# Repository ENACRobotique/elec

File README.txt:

Repository for electronic circuits design

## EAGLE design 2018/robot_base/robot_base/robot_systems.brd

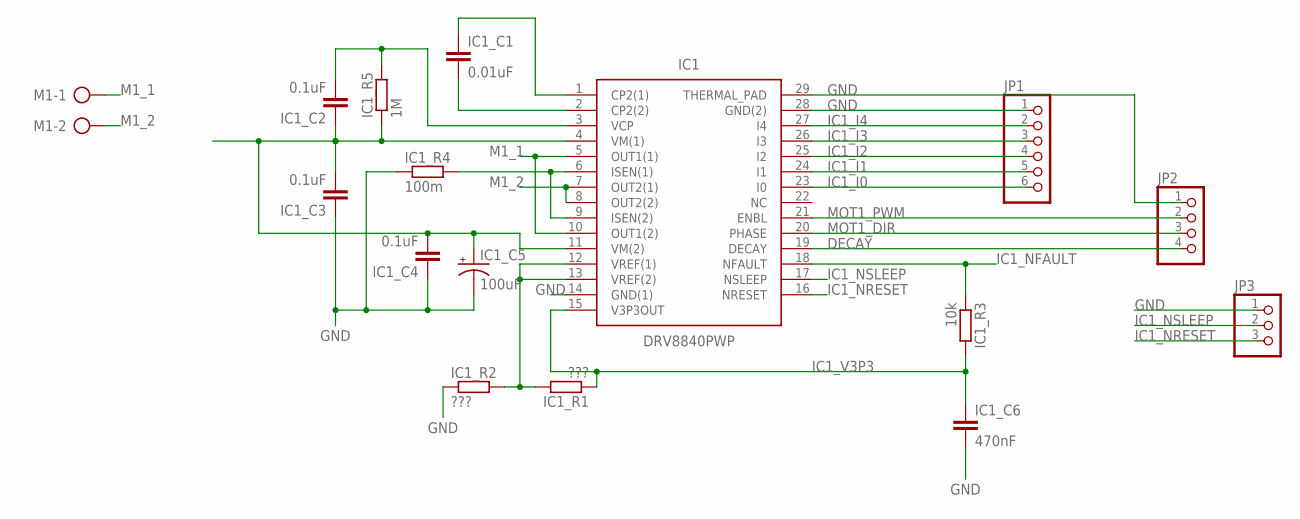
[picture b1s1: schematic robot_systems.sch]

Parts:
IC1: DRV8840PWP; SOP65P640X120-29N
IC1_C1: 0.01uF; C0603
IC1_C2, IC1_C3: 0.1uF; 0805
IC1_C4: 0.1uF; 1206
IC1_C5: 100uF; EIA7343
IC1_C6: 470nF; C0603
IC1_R1, IC1_R2: ???; 0204/5
IC1_R3: 10k; R2010
IC1_R4: 100m; R2512
IC1_R5: 1M; R0603
JP1: PINHD-1X6; 1X06
JP2: PINHD-1X4; 1X04
JP3: PINHD-1X3; 1X03
M1: AK500/2

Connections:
12V2: IC1.4 (VM(1)), IC1.11 (VM(2)), IC1_C2.1, IC1_C3.2, IC1_C4.2, IC1_C5.A (+), IC1_R5.1
DECAY: IC1.19 (DECAY), JP2.4
GND: IC1.14 (GND(1)), IC1.28 (GND(2)), IC1.29 (THERMAL_PAD), IC1_C3.1, IC1_C4.1, IC1_C5.C (-), IC1_C6.2, IC1_R2.1, IC1_R4.1, JP1.1, JP2.1, JP3.1
IC1_I0: IC1.23 (I0), JP1.6
IC1_I1: IC1.24 (I1), JP1.5
IC1_I2: IC1.25 (I2), JP1.4
IC1_I3: IC1.26 (I3), JP1.3
IC1_I4: IC1.27 (I4), JP1.2
IC1_NFAULT: IC1.18 (NFAULT), IC1_R3.1
IC1_NRESET: IC1.16 (NRESET), JP3.3
IC1_NSLEEP: IC1.17 (NSLEEP), JP3.2
IC1_V3P3: IC1.15 (V3P3OUT), IC1_C6.1, IC1_R1.1, IC1_R3.2
M1_1: IC1.5 (OUT1(1)), IC1.10 (OUT1(2)), M1.1
M1_2: IC1.7 (OUT2(1)), IC1.8 (OUT2(2)), M1.2
MOT1_DIR: IC1.20 (PHASE), JP2.3
MOT1_PWM: IC1.21 (ENBL), JP2.2
unnamed: IC1.12 (VREF(1)), IC1.13 (VREF(2)), IC1_R1.2, IC1_R2.2
unnamed: IC1.6 (ISEN(1)), IC1.9 (ISEN(2)), IC1_R4.2
unnamed: IC1.1 (CP2(1)), IC1_C1.1
unnamed: IC1.2 (CP2(2)), IC1_C1.2
unnamed: IC1.3 (VCP), IC1_C2.2, IC1_R5.2

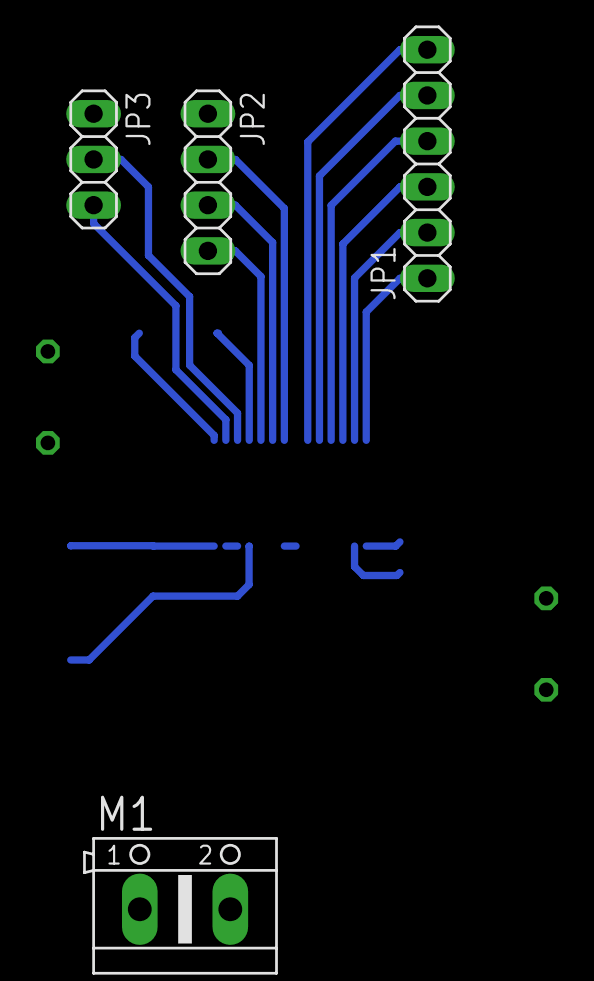
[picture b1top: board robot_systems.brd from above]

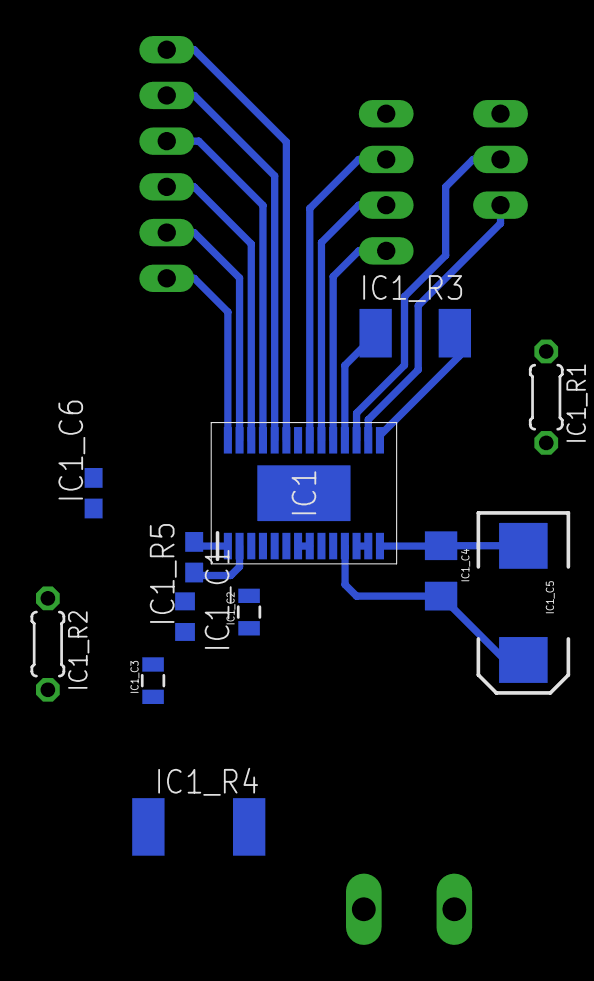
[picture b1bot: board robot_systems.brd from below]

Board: 2 copper layers, 16 parts (12 on the bottom side), 21 nets.

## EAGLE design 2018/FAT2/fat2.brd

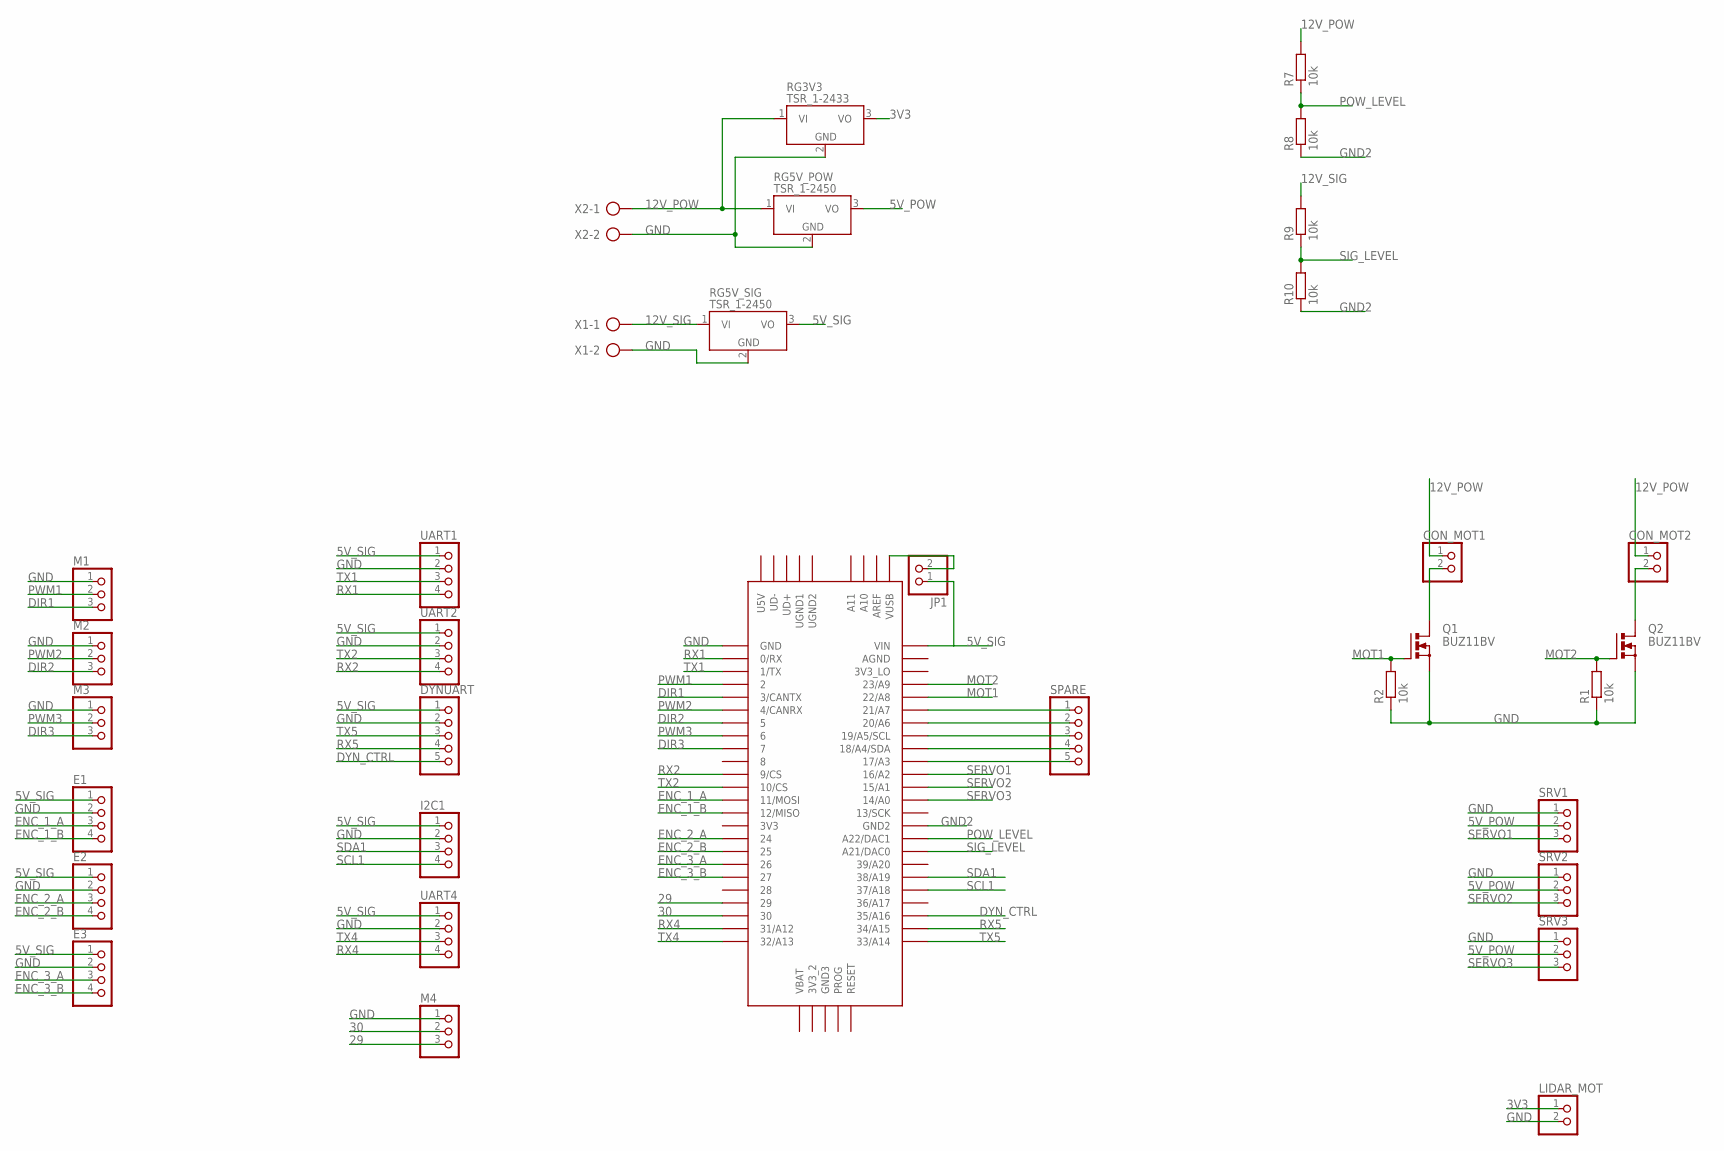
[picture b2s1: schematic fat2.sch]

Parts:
CON_MOT1, CON_MOT2: PINHD-1X2; 1X02
DYNUART: PINHD-1X5; 1X05
E1, E2, E3: PINHD-1X4; 1X04
I2C1: PINHD-1X4; 1X04
JP1: PINHD-1X2/90; 1X02/90
LIDAR_MOT: PINHD-1X2; 1X02
M1, M2, M3, M4: PINHD-1X3; 1X03
Q1, Q2: BUZ11BV; TO220BV
R1, R2, R7, R8, R9, R10: 10k; 0204/7
RG3V3: TSR_1-2433; TSR-1
RG5V_POW, RG5V_SIG: TSR_1-2450; TSR-1
SPARE: PINHD-1X5; 1X05
SRV1, SRV2, SRV3: PINHD-1X3; 1X03
U$1: TEENSY_3.5/3.6
UART1, UART2, UART4: PINHD-1X4; 1X04
X1, X2: AK300/2

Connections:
3V3: LIDAR_MOT.1, RG3V3.3 (VO)
5V_POW: RG5V_POW.3 (VO), SRV1.2, SRV2.2, SRV3.2
5V_SIG: DYNUART.1, E1.1, E2.1, E3.1, I2C1.1, JP1.1, RG5V_SIG.3 (VO), U$1.VIN, UART1.1, UART2.1, UART4.1
12V_POW: CON_MOT1.1, CON_MOT2.1, R7.2, RG3V3.1 (VI), RG5V_POW.1 (VI), X2.1
12V_SIG: R9.2, RG5V_SIG.1 (VI), X1.1
29: M4.3, U$1.29
30: M4.2, U$1.30
DIR1: M1.3, U$1.3/CANTX
DIR2: M2.3, U$1.5
DIR3: M3.3, U$1.7
DYN_CTRL: DYNUART.5, U$1.35/A16
ENC_1_A: E1.3, U$1.11/MOSI
ENC_1_B: E1.4, U$1.12/MISO
ENC_2_A: E2.3, U$1.24
ENC_2_B: E2.4, U$1.25
ENC_3_A: E3.3, U$1.26
ENC_3_B: E3.4, U$1.27
GND: DYNUART.2, E1.2, E2.2, E3.2, I2C1.2, LIDAR_MOT.2, M1.1, M2.1, M3.1, M4.1, Q1.S, Q2.S, R1.1, R2.1, RG3V3.2 (GND), RG5V_POW.2 (GND), RG5V_SIG.2 (GND), SRV1.1, SRV2.1, SRV3.1, U$1.GND, UART1.2, UART2.2, UART4.2, X1.2, X2.2
GND2: R8.1, R10.1, U$1.GND2
MOT1: Q1.G, R2.2, U$1.22/A8
MOT2: Q2.G, R1.2, U$1.23/A9
unnamed: SPARE.5, U$1.17/A3
unnamed: SPARE.4, U$1.18/A4/SDA
unnamed: CON_MOT1.2, Q1.D
unnamed: SPARE.3, U$1.19/A5/SCL
unnamed: CON_MOT2.2, Q2.D
unnamed: SPARE.2, U$1.20/A6
unnamed: JP1.2, U$1.VUSB
unnamed: SPARE.1, U$1.21/A7
POW_LEVEL: R7.1, R8.2, U$1.A22/DAC1
PWM1: M1.2, U$1.2
PWM2: M2.2, U$1.4/CANRX
PWM3: M3.2, U$1.6
RX1: U$1.0/RX, UART1.4
RX2: U$1.9/CS, UART2.4
RX4: U$1.31/A12, UART4.4
RX5: DYNUART.4, U$1.34/A15
SCL1: I2C1.4, U$1.37/A18
SDA1: I2C1.3, U$1.38/A19
SERVO1: SRV1.3, U$1.16/A2
SERVO2: SRV2.3, U$1.15/A1
SERVO3: SRV3.3, U$1.14/A0
SIG_LEVEL: R9.1, R10.2, U$1.21/DAC0 (A21/DAC0)
TX1: U$1.1/TX, UART1.3
TX2: U$1.10/CS, UART2.3
TX4: U$1.32/A13, UART4.3
TX5: DYNUART.3, U$1.33/A14

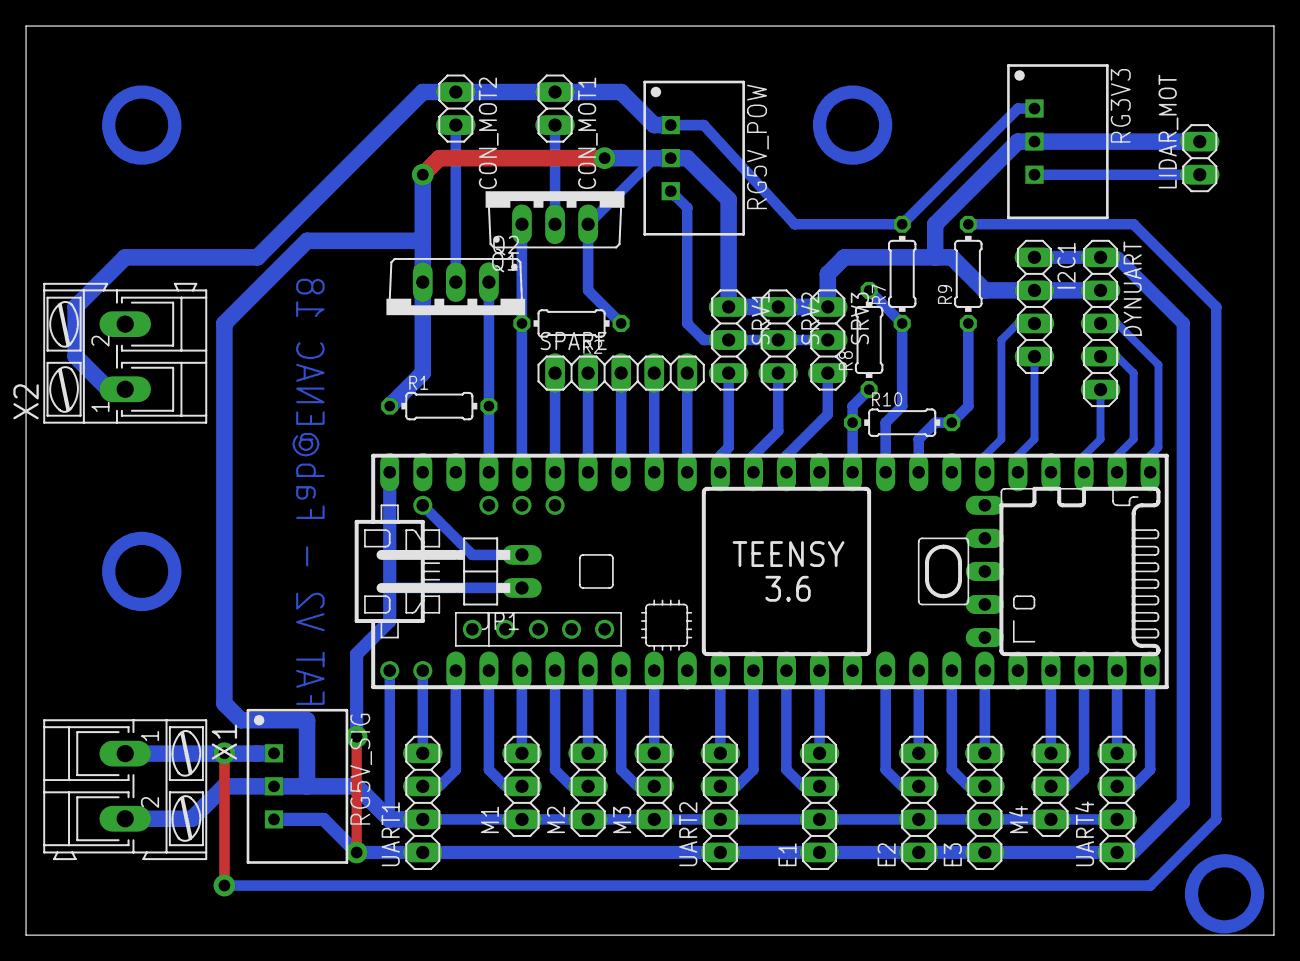
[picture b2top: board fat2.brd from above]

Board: 2 copper layers, 95.9 x 69.8 mm, 34 parts (0 on the bottom side), 47 nets.

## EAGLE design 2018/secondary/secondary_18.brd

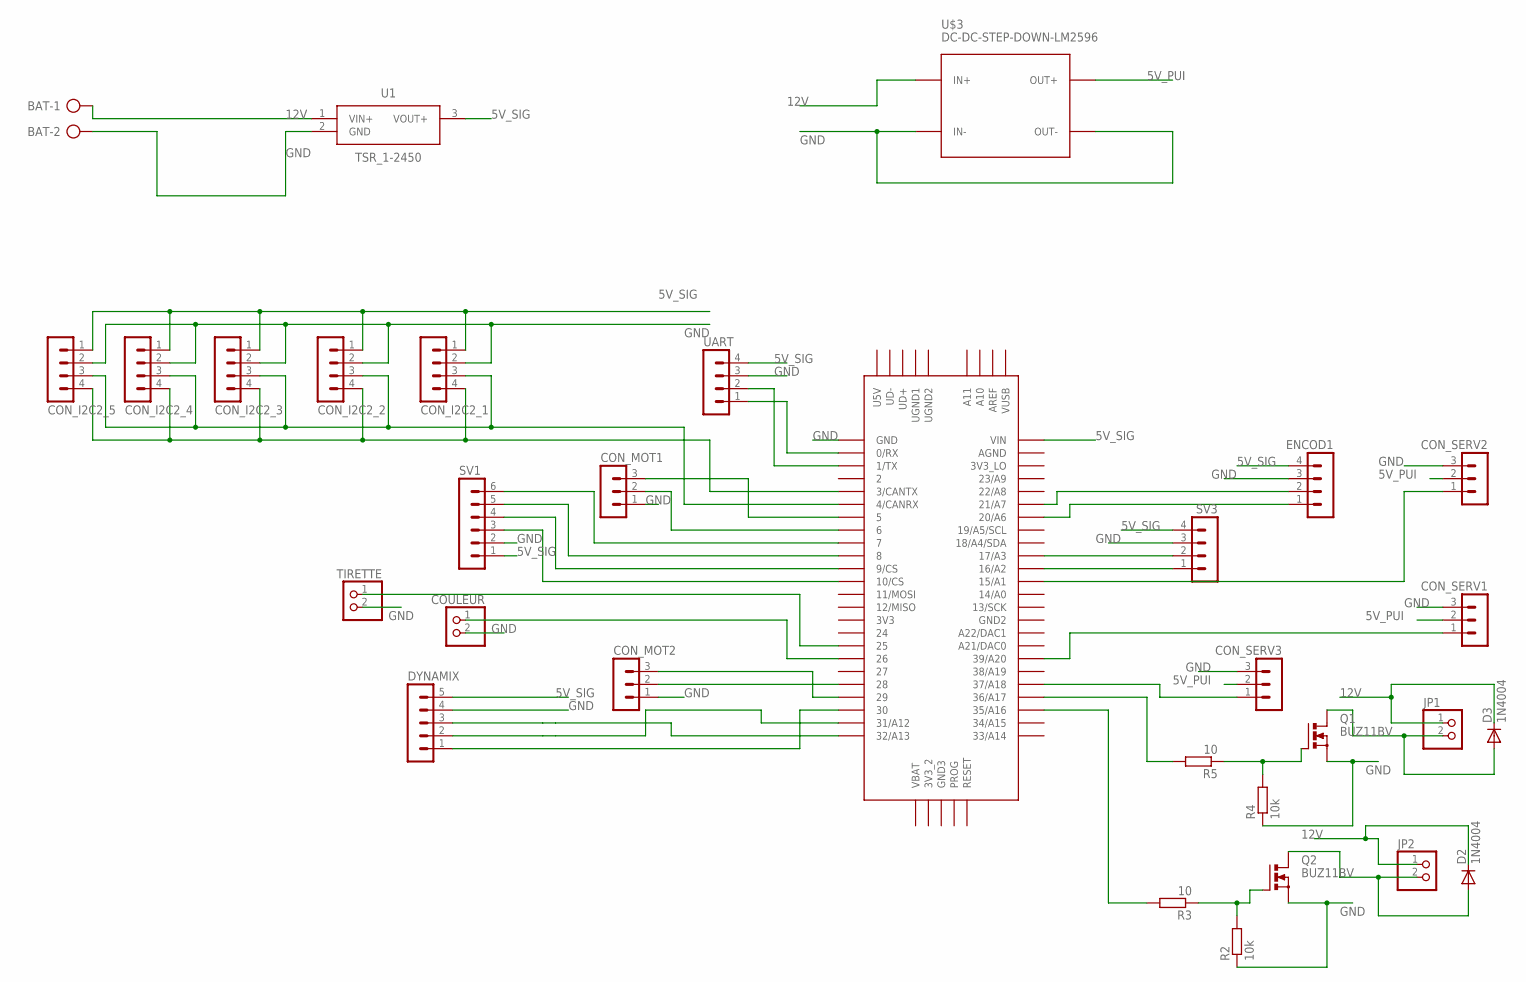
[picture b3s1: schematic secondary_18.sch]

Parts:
BAT: AK300/2
CON_I2C2_1, CON_I2C2_2, CON_I2C2_3, CON_I2C2_4, CON_I2C2_5: MA04-1
CON_MOT1, CON_MOT2: MA03-1
CON_SERV1, CON_SERV2, CON_SERV3: MA03-1
COULEUR: PINHD-1X2; 1X02
D2, D3: 1N4004; DO41-10
DYNAMIX: MA05-1
ENCOD1: MA04-1
JP1, JP2: PINHD-1X2; 1X02
Q1, Q2: BUZ11BV; TO220BV
R2, R4: 10k; 0204/7
R3, R5: 10; 0204/7
SV1: MA06-1
SV3: MA04-1
TIRETTE: PINHD-1X2; 1X02
U1: TSR_1-2450; TSR-1-24120
U$1: TEENSY_3.5/3.6
U$3: DC-DC-STEP-DOWN-LM2596
UART: MA04-1

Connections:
5V_PUI: CON_SERV1.2, CON_SERV2.2, CON_SERV3.2, U$3.OUT+
5V_SIG: CON_I2C2_1.1, CON_I2C2_2.1, CON_I2C2_3.1, CON_I2C2_4.1, CON_I2C2_5.1, DYNAMIX.5, ENCOD1.4, SV1.1, SV3.4, U1.3 (VOUT+), U$1.VIN, UART.4
12V: BAT.1, D2.C, D3.C, JP1.1, JP2.1, U1.1 (VIN+), U$3.IN+
GND: BAT.2, CON_I2C2_1.2, CON_I2C2_2.2, CON_I2C2_3.2, CON_I2C2_4.2, CON_I2C2_5.2, CON_MOT1.1, CON_MOT2.1, CON_SERV1.3, CON_SERV2.3, CON_SERV3.3, COULEUR.2, DYNAMIX.4, ENCOD1.3, Q1.S, Q2.S, R2.1, R4.1, SV1.2, SV3.3, TIRETTE.2, U1.2 (GND), U$1.GND, U$3.IN-, U$3.OUT-, UART.3
unnamed: CON_MOT2.3, U$1.29
unnamed: CON_MOT1.3, U$1.5
unnamed: CON_MOT1.2, U$1.6
unnamed: CON_MOT2.2, U$1.28
unnamed: Q2.G, R2.2, R3.1
unnamed: R3.2, U$1.35/A16
unnamed: D2.A, JP2.2, Q2.D
unnamed: SV3.1, U$1.16/A2
unnamed: Q1.G, R4.2, R5.1
unnamed: R5.2, U$1.36/A17
unnamed: D3.A, JP1.2, Q1.D
unnamed: SV3.2, U$1.17/A3
unnamed: ENCOD1.1, U$1.20/A6
unnamed: ENCOD1.2, U$1.21/A7
unnamed: CON_SERV2.1, U$1.15/A1
unnamed: CON_SERV3.1, U$1.37/A18
unnamed: DYNAMIX.3, U$1.32/A13
unnamed: CON_SERV1.1, U$1.39/A20
unnamed: DYNAMIX.2, U$1.31/A12
unnamed: CON_I2C2_1.4, CON_I2C2_2.4, CON_I2C2_3.4, CON_I2C2_4.4, CON_I2C2_5.4, U$1.3/CANTX
unnamed: COULEUR.1, U$1.26
unnamed: CON_I2C2_1.3, CON_I2C2_2.3, CON_I2C2_3.3, CON_I2C2_4.3, CON_I2C2_5.3, U$1.4/CANRX
unnamed: DYNAMIX.1, U$1.30
unnamed: TIRETTE.1, U$1.25
unnamed: U$1.1/TX, UART.2
unnamed: U$1.0/RX, UART.1
unnamed: SV1.3, U$1.10/CS
unnamed: SV1.4, U$1.9/CS
unnamed: SV1.5, U$1.8
unnamed: SV1.6, U$1.7

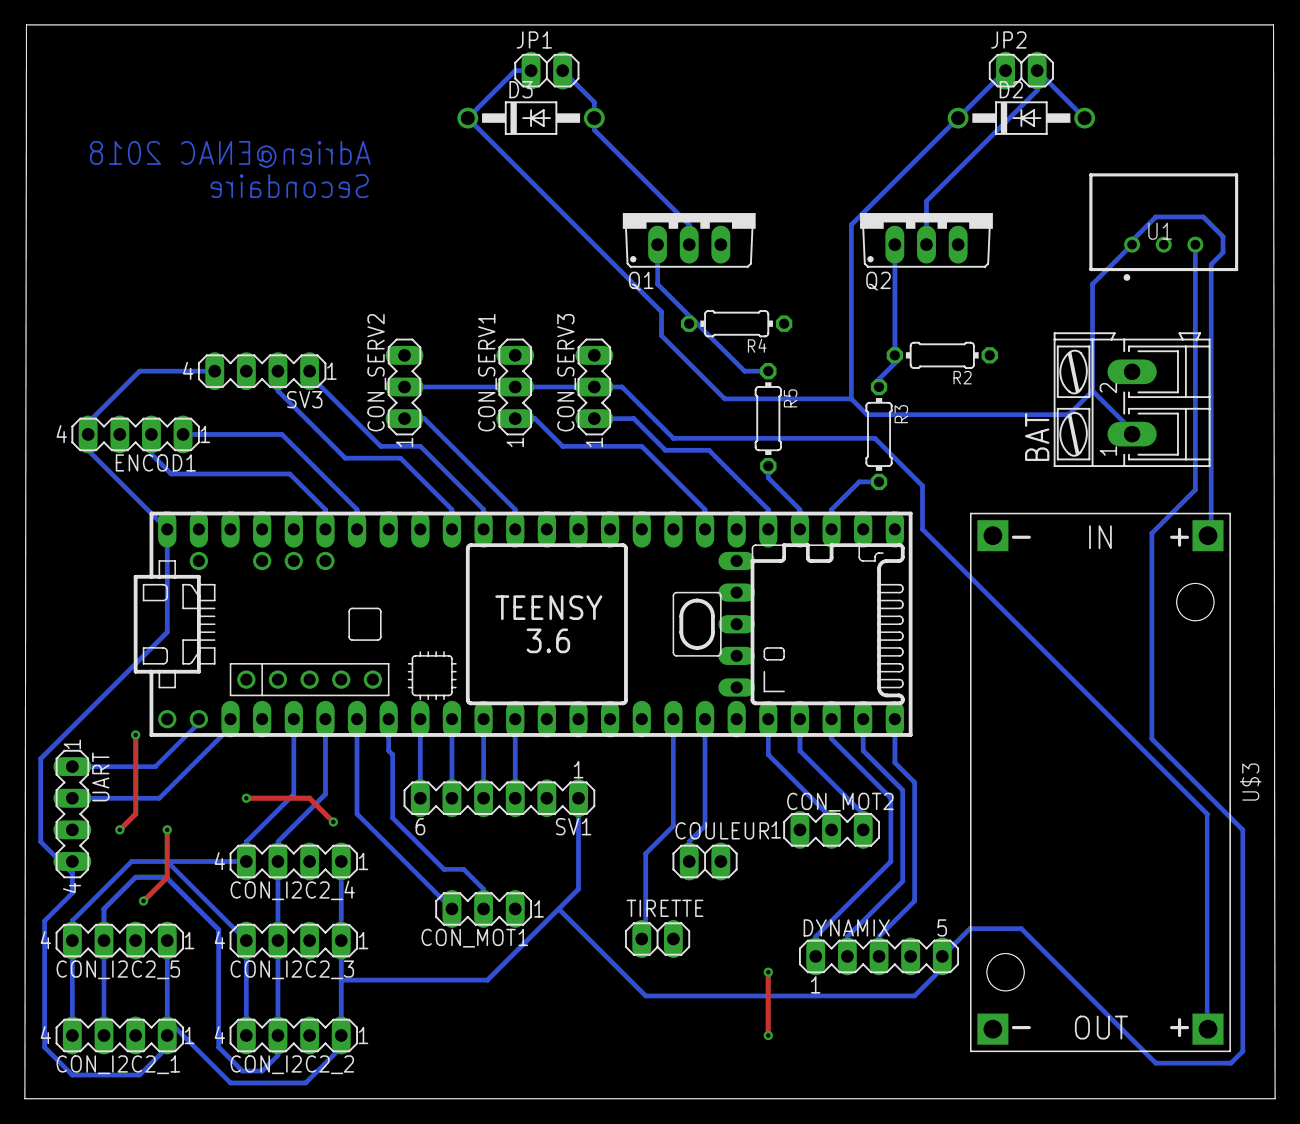
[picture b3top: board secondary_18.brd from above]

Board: 2 copper layers, 100.4 x 86.2 mm, 31 parts (0 on the bottom side), 34 nets.

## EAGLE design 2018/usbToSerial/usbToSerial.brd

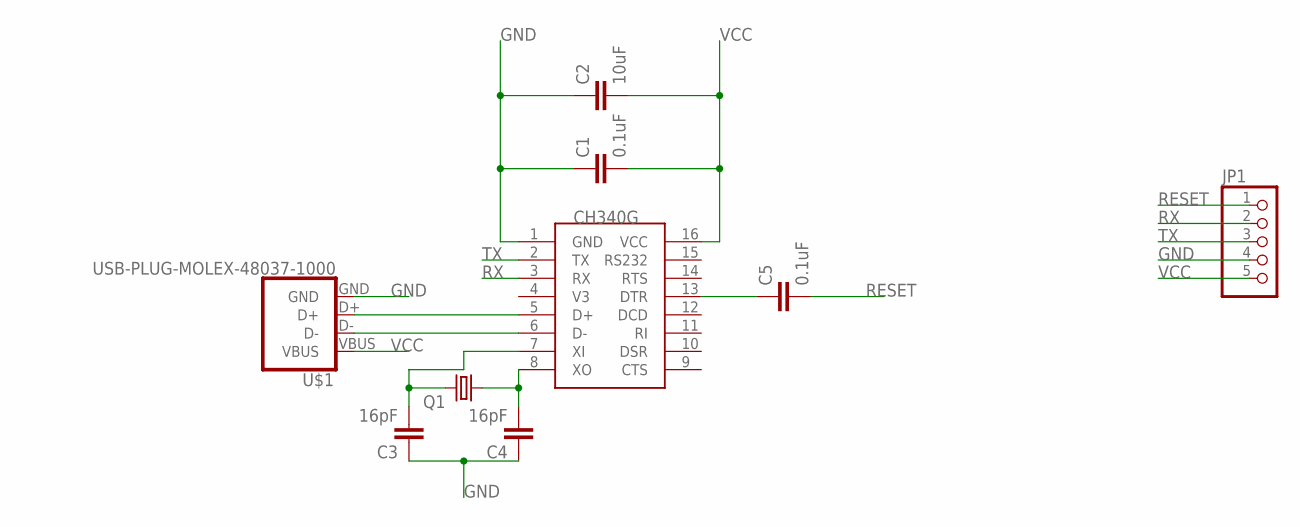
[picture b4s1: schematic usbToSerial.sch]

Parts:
C1, C5: 0.1uF; C0603
C2: 10uF; C3216
C3, C4: 16pF; C0603
JP1: PINHD-1X5/90; 1X05/90
Q1: CRYSTALSM49; SM49
U$1: USB-PLUG-MOLEX-48037-1000; MOLEX-48037-1000
U$2: CH340G; SOIC16

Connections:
GND: C1.1, C2.1, C3.1, C4.1, JP1.4, U$1.GND, U$2.1 (GND)
unnamed: U$1.D+, U$2.5 (D+)
unnamed: U$1.D-, U$2.6 (D-)
unnamed: C3.2, Q1.2, U$2.7 (XI)
unnamed: C4.2, Q1.1, U$2.8 (XO)
unnamed: C5.1, U$2.13 (DTR)
RESET: C5.2, JP1.1
RX: JP1.2, U$2.3 (RX)
TX: JP1.3, U$2.2 (TX)
VCC: C1.2, C2.2, JP1.5, U$1.VBUS, U$2.16 (VCC)

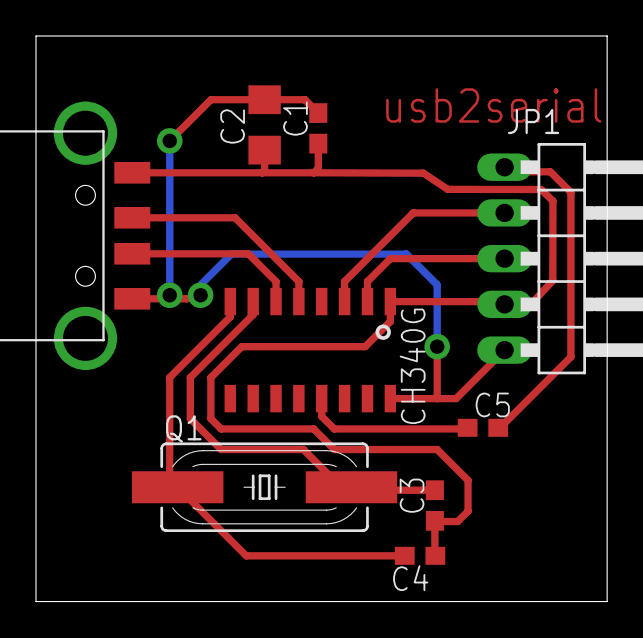
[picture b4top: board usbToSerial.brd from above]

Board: 2 copper layers, 31.7 x 31.4 mm, 9 parts (0 on the bottom side), 10 nets.

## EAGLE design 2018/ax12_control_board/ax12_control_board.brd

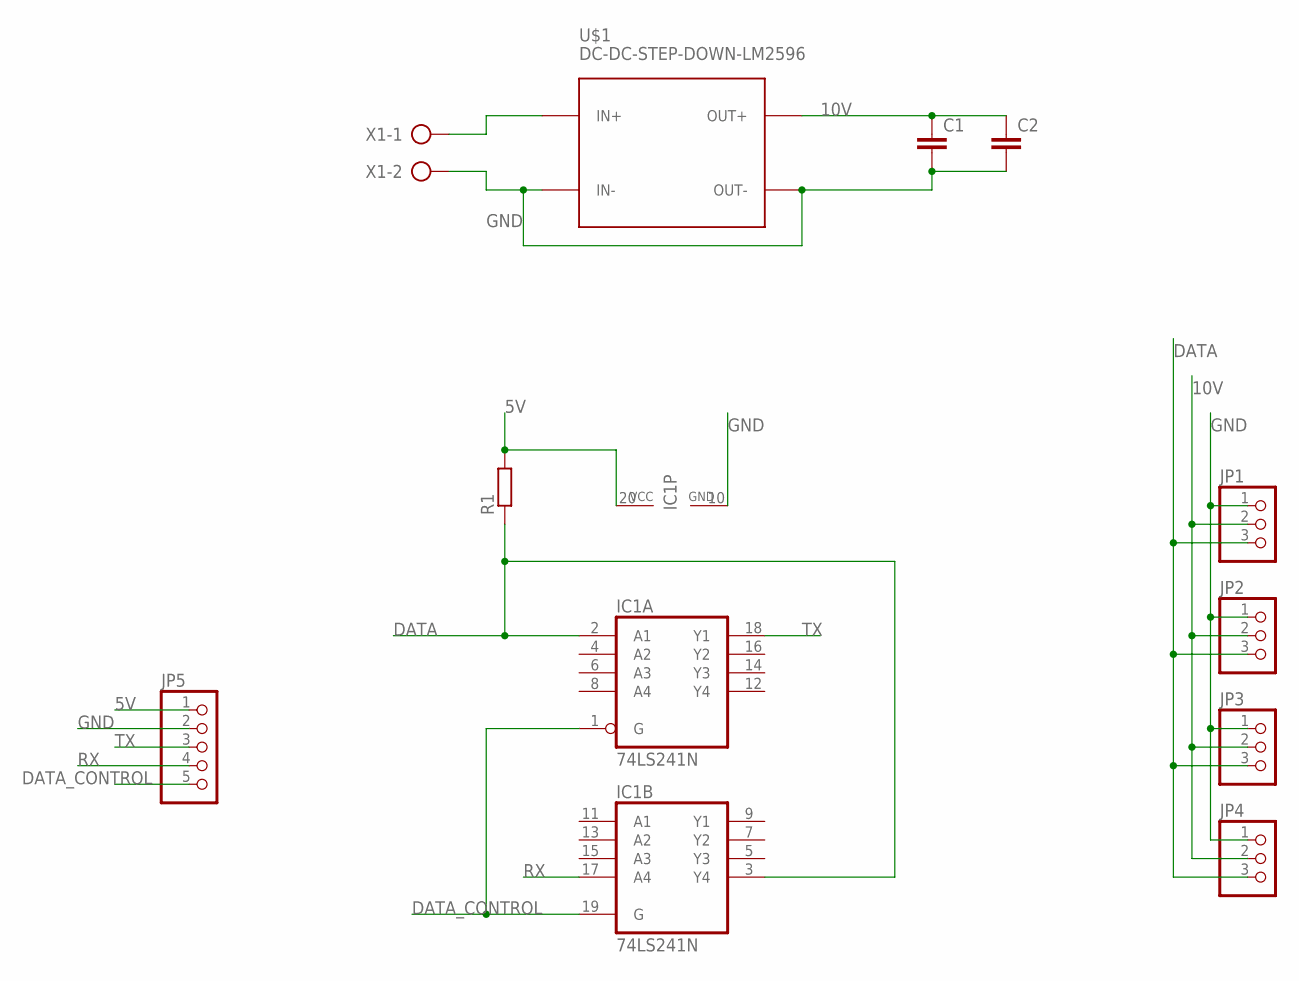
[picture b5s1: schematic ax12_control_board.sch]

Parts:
C1, C2: C-EU025-060X050; C025-060X050
IC1: 74LS241N; DIL20
JP1, JP2, JP3, JP4: PINHD-1X3; 1X03
JP5: PINHD-1X5; 1X05
R1: R-EU_0207/12; 0207/12
U$1: DC-DC-STEP-DOWN-LM2596
X1: AK300/2

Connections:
5V: IC1.20 (VCC), JP5.1, R1.2
10V: C1.1, C2.1, JP1.2, JP2.2, JP3.2, JP4.2, U$1.OUT+
DATA: IC1.2 (A1), IC1.3 (Y4), JP1.3, JP2.3, JP3.3, JP4.3, R1.1
DATA_CONTROL: IC1.1 (G), IC1.19 (G), JP5.5
GND: C1.2, C2.2, IC1.10 (GND), JP1.1, JP2.1, JP3.1, JP4.1, JP5.2, U$1.IN-, U$1.OUT-, X1.2
unnamed: U$1.IN+, X1.1
RX: IC1.17 (A4), JP5.4
TX: IC1.18 (Y1), JP5.3

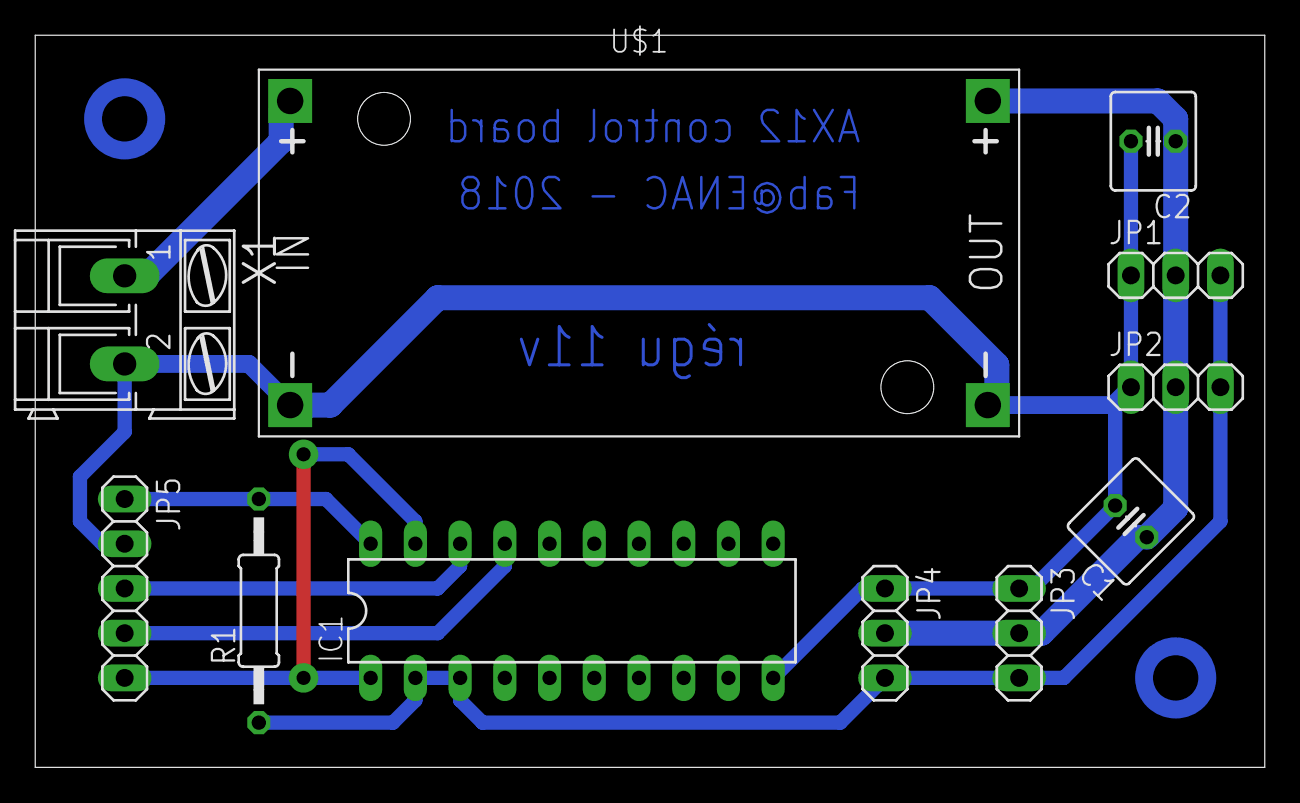
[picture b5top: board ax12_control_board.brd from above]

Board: 2 copper layers, 69.8 x 41.6 mm, 11 parts (0 on the bottom side), 8 nets.

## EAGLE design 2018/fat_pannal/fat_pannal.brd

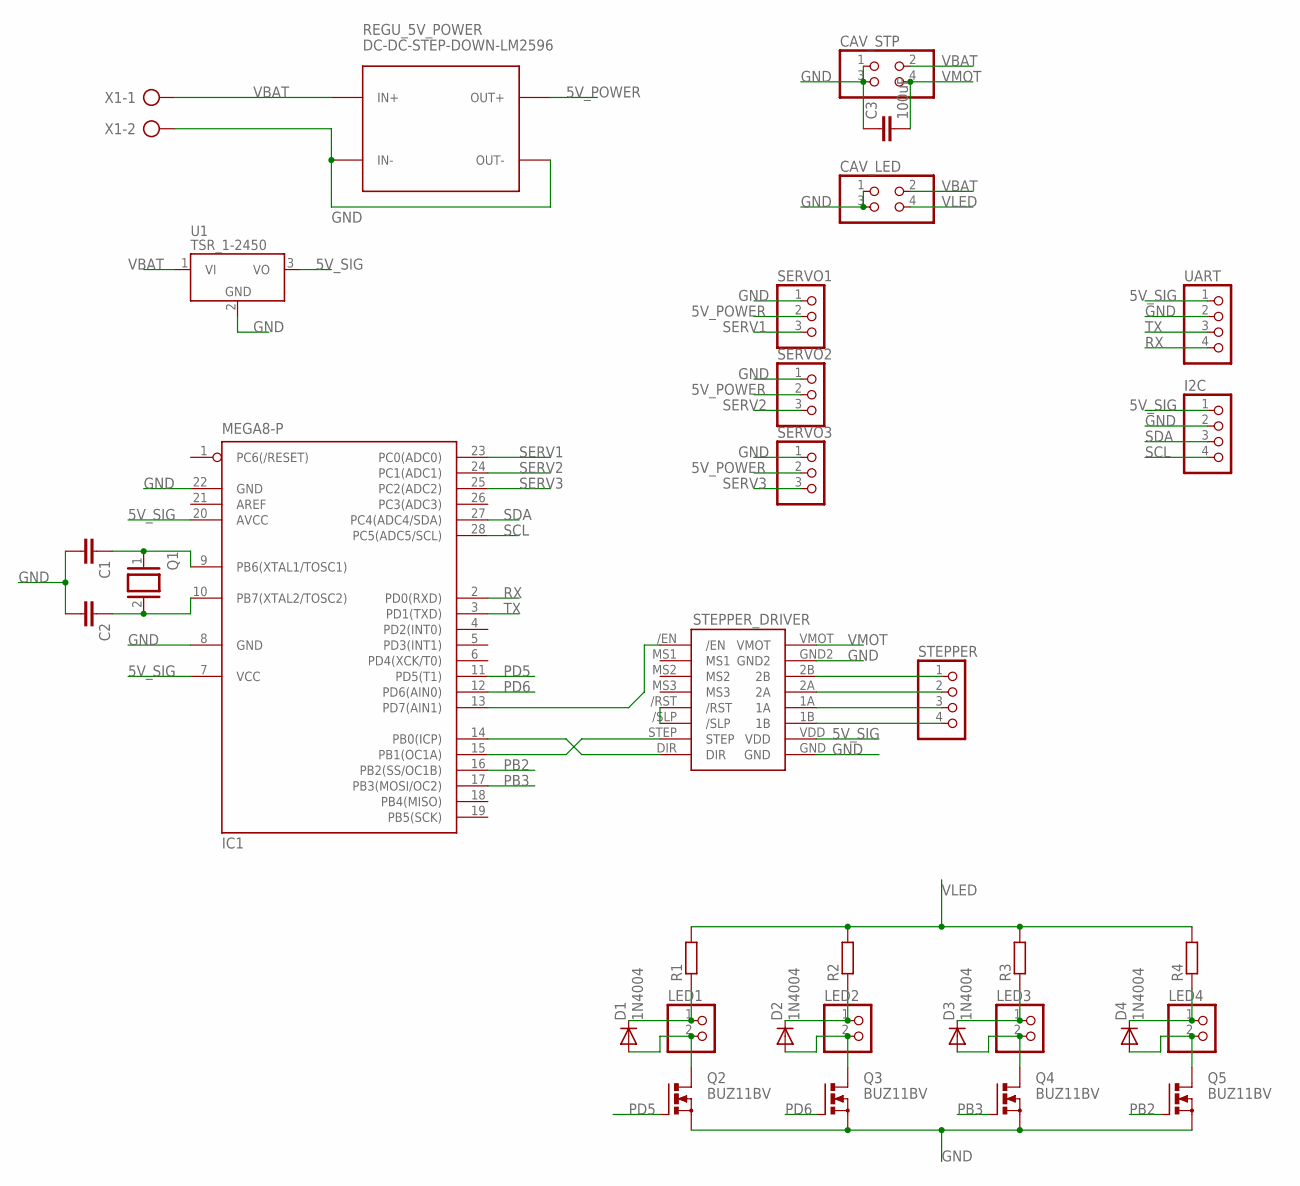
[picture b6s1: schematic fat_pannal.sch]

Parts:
C1, C2: C-EU025-030X050; C025-030X050
C3: 100uF; C025-050X050
CAV_LED: PINHD-2X2; 2X02
CAV_STP: PINHD-2X2; 2X02
D1, D2, D3, D4: 1N4004; DO41-10
I2C: PINHD-1X4; 1X04
IC1: MEGA8-P; DIL28-3
LED1, LED2, LED3, LED4: PINHD-1X2; 1X02
Q1: XTAL/S; QS
Q2, Q3, Q4, Q5: BUZ11BV; TO220BV
R1, R2, R3, R4: R-EU_0309/12; 0309/12
REGU_5V_POWER: DC-DC-STEP-DOWN-LM2596
SERVO1, SERVO2, SERVO3: PINHD-1X3; 1X03
STEPPER: PINHD-1X4; 1X04
STEPPER_DRIVER: A4988_CARRIER
U1: TSR_1-2450; TSR-1
UART: PINHD-1X4; 1X04
X1: AK300/2

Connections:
5V_POWER: REGU_5V_POWER.OUT+, SERVO1.2, SERVO2.2, SERVO3.2
5V_SIG: I2C.1, IC1.7 (VCC), IC1.20 (AVCC), STEPPER_DRIVER.VDD, U1.3 (VO), UART.1
GND: C1.2, C2.2, C3.1, CAV_LED.1, CAV_LED.3, CAV_STP.1, CAV_STP.3, I2C.2, IC1.8 (GND), IC1.22 (GND), Q2.S, Q3.S, Q4.S, Q5.S, REGU_5V_POWER.IN-, REGU_5V_POWER.OUT-, SERVO1.1, SERVO2.1, SERVO3.1, STEPPER_DRIVER.GND, STEPPER_DRIVER.GND2, U1.2 (GND), UART.2, X1.2
unnamed: C1.1, IC1.9 (PB6(XTAL1/TOSC1)), Q1.1
unnamed: IC1.15 (PB1(OC1A)), STEPPER_DRIVER.STEP
unnamed: C2.1, IC1.10 (PB7(XTAL2/TOSC2)), Q1.2
unnamed: IC1.14 (PB0(ICP)), STEPPER_DRIVER.DIR
unnamed: STEPPER_DRIVER./RST, STEPPER_DRIVER./SLP
unnamed: IC1.13 (PD7(AIN1)), STEPPER_DRIVER./EN
unnamed: STEPPER.4, STEPPER_DRIVER.1B
unnamed: STEPPER.3, STEPPER_DRIVER.1A
unnamed: STEPPER.2, STEPPER_DRIVER.2A
unnamed: STEPPER.1, STEPPER_DRIVER.2B
unnamed: D1.C, LED1.1, R1.1
unnamed: D2.C, LED2.1, R2.1
unnamed: D3.C, LED3.1, R3.1
unnamed: D4.C, LED4.1, R4.1
unnamed: D1.A, LED1.2, Q2.D
unnamed: D2.A, LED2.2, Q3.D
unnamed: D3.A, LED3.2, Q4.D
unnamed: D4.A, LED4.2, Q5.D
PB2: IC1.16 (PB2(SS/OC1B)), Q5.G
PB3: IC1.17 (PB3(MOSI/OC2)), Q4.G
PD5: IC1.11 (PD5(T1)), Q2.G
PD6: IC1.12 (PD6(AIN0)), Q3.G
RX: IC1.2 (PD0(RXD)), UART.4
SCL: I2C.4, IC1.28 (PC5(ADC5/SCL))
SDA: I2C.3, IC1.27 (PC4(ADC4/SDA))
SERV1: IC1.23 (PC0(ADC0)), SERVO1.3
SERV2: IC1.24 (PC1(ADC1)), SERVO2.3
SERV3: IC1.25 (PC2(ADC2)), SERVO3.3
TX: IC1.3 (PD1(TXD)), UART.3
VBAT: CAV_LED.2, CAV_STP.2, REGU_5V_POWER.IN+, U1.1 (VI), X1.1
VLED: CAV_LED.4, R1.2, R2.2, R3.2, R4.2
VMOT: C3.2, CAV_STP.4, STEPPER_DRIVER.VMOT

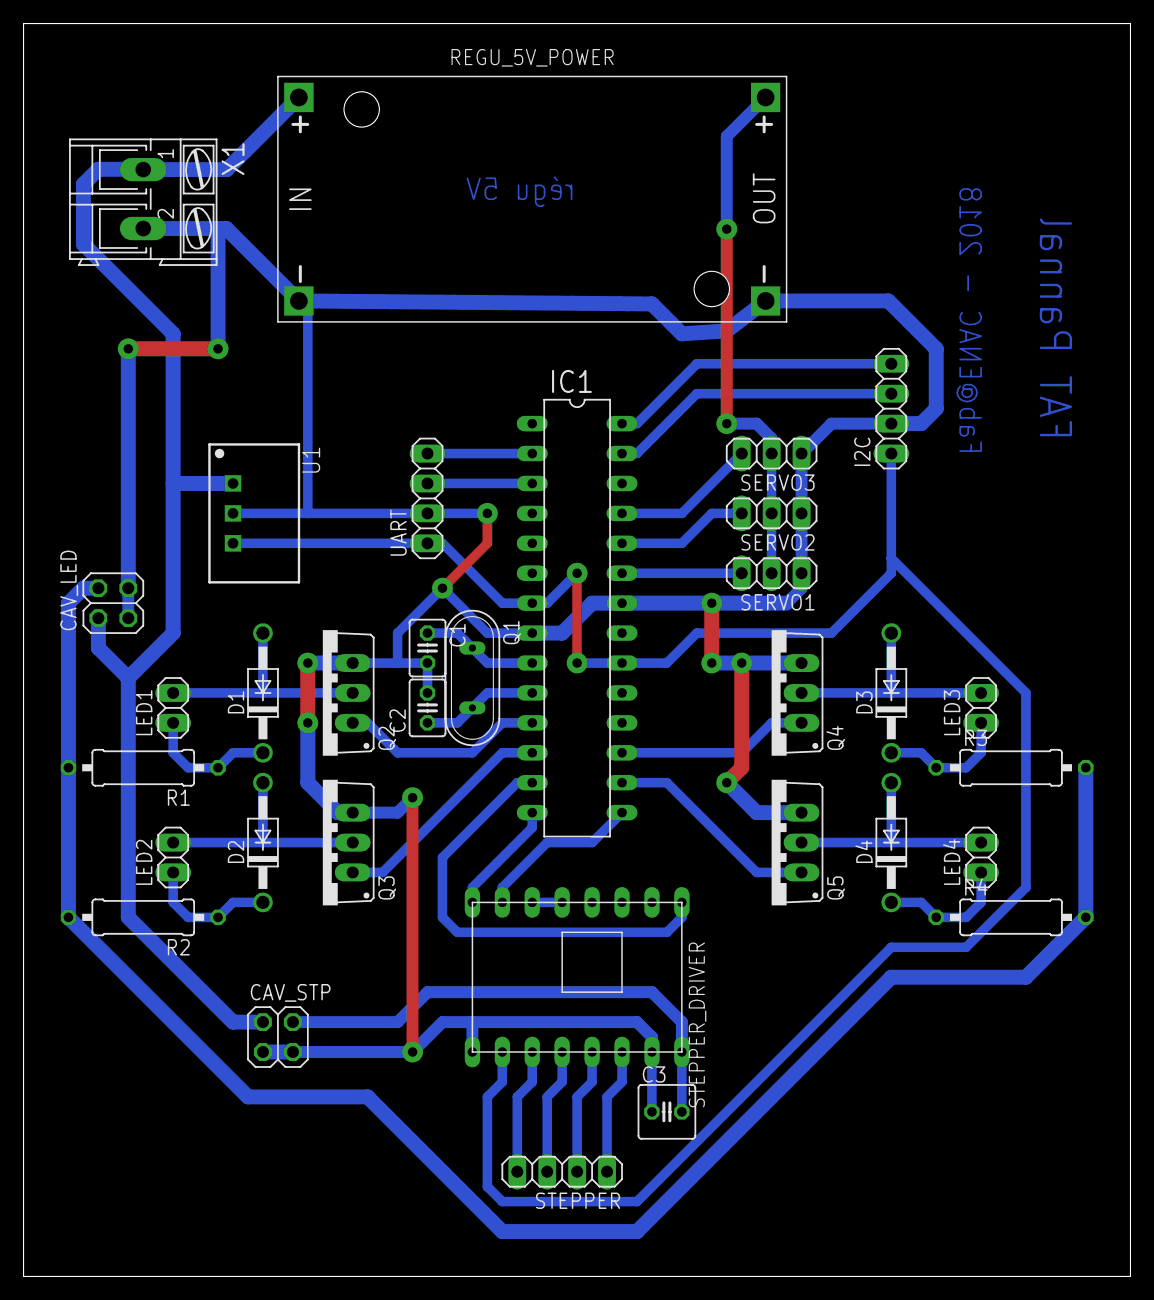
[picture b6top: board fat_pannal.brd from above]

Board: 2 copper layers, 94.0 x 106.3 mm, 33 parts (0 on the bottom side), 35 nets.

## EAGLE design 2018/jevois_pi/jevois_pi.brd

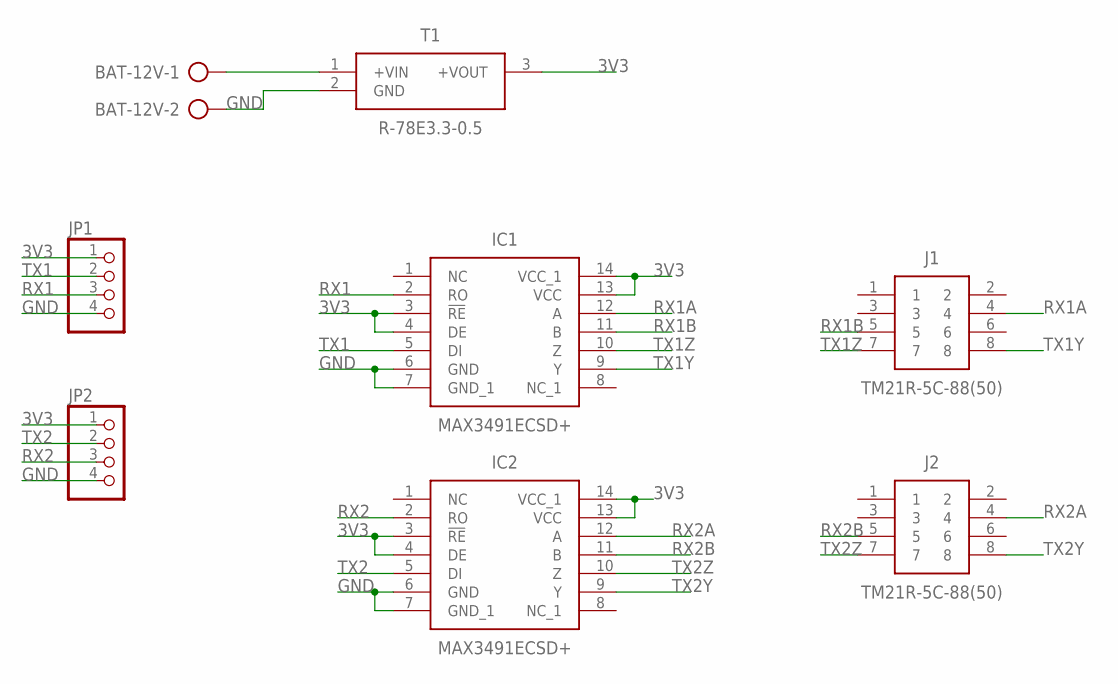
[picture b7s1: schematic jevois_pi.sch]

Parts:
BAT-12V: AK500/2-H
IC1, IC2: MAX3491ECSD+; SOIC127P600X175-14N
J1, J2: TM21R-5C-88(50)
JP1, JP2: PINHD-1X4; 1X04
T1: R-78E3.3-0.5; SHDRV3W100P0_254_1X3_1160X850X

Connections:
3V3: IC1.3 (!RE), IC1.4 (DE), IC1.13 (VCC), IC1.14 (VCC_1), IC2.3 (!RE), IC2.4 (DE), IC2.13 (VCC), IC2.14 (VCC_1), JP1.1, JP2.1, T1.3 (+VOUT)
GND: BAT-12V.2, IC1.6 (GND), IC1.7 (GND_1), IC2.6 (GND), IC2.7 (GND_1), JP1.4, JP2.4, T1.2 (GND)
unnamed: BAT-12V.1, T1.1 (+VIN)
RX1: IC1.2 (RO), JP1.3
RX1A: IC1.12 (A), J1.4
RX1B: IC1.11 (B), J1.5
RX2: IC2.2 (RO), JP2.3
RX2A: IC2.12 (A), J2.4
RX2B: IC2.11 (B), J2.5
TX1: IC1.5 (DI), JP1.2
TX1Y: IC1.9 (Y), J1.8
TX1Z: IC1.10 (Z), J1.7
TX2: IC2.5 (DI), JP2.2
TX2Y: IC2.9 (Y), J2.8
TX2Z: IC2.10 (Z), J2.7

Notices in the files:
parts and their libraries:
diy-modules: Released under the Creative Commons Attribution 4.0 International License: http://creativecommons.org/licenses/by/4.0
SparkFun-Passives: Licensing: Creative Commons ShareAlike 4.0 International - https://creativecommons.org/licenses/by-sa/4.0
